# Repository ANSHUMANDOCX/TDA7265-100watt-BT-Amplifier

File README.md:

# TDA7265 100 watt DUAL IC BT Amplifier 

This is a BT amp which has a max ouput of 100watt (50+50) and BT input for audio

# Parts
- TDA7265 IC x2
- MH-M18
- 12-0-12 Transformer

# Plan
I always wanted to make a powerful enough speakers to use with my Sony speaker. Now i have found a appropriate ic which can be tweaked to to get a max output of 50 watt in each channel hence 100watt total TDP.

I have use a MH-M18 BT module which is both cheap and provides lossless audio

i had made a TDA7269A amp which was a 14+14 watt Amp so this is a massive upgrade to it.

# BOM
| S.No | Description                       | Quantity | Total Price | Supplier |LINK|
|------|-----------------------------------|----------|-------------|----------|-------------------------------|
| 1    | Capacitors |         | $3.64       | LCSC    |https://lcsc.com/product-detail/Aluminum-Electrolytic-Capacitors-Leaded_AISHI-ERR1VM102G20OT_C398835.html  https://lcsc.com/product-detail/image/50YXF1MEFC5X11_C2927584.html  https://lcsc.com/product-detail/Aluminum-Electrolytic-Capacitors-Leaded_Rubycon-50YXF1MEFC5X11_C2927584.html  https://lcsc.com/product-detail/Aluminum-Electrolytic-Capacitors-Leaded_Rubycon-50YXF10MEFC5X11_C88726.htmldc  https://lcsc.com/product-detail/Film-Capacitors_KYET-PE104J2A0501_C390170.html  https://lcsc.com/product-detail/Film-Capacitors_WEIDY-W242A562JD2TAAA4JA_C7502419.html|
| 2    | Resistor  | 5        | $3.03       | LCSC    |https://lcsc.com/product-detail/Through-Hole-Resistors_VO-MF1-4W-36K-1-ST52_C2848587.html  https://lcsc.com/product-detail/Through-Hole-Resistors_YAGEO-MFR-25FBF52-560R_C1369978.html  https://lcsc.com/product-detail/Through-Hole-Resistors_CCO-Chian-Chia-Elec-CF1-4W-4-7-5-T_C119999.html  https://lcsc.com/product-detail/Through-Hole-Resistors_Huaxing-Mechanical-Elec-MF1-4W-1K-1-T52_C713997.html  https://lcsc.com/product-detail/Through-Hole-Resistors_VO-MF1-4W-10K-1-ST52_C2903232.html|
| 3    | Diode   | 5        | $0.81      | LCSC    |https://lcsc.com/product-detail/Diodes-General-Purpose_LGE-6A4_C5369359.html|
| 4    | Regulator ICs | 5        | $2.77       | LCSC    |https://lcsc.com/product-detail/Voltage-Regulators-Linear-Low-Drop-Out-LDO-Regulators_ST-L7912CV-DG_C3797.html  https://lcsc.com/product-detail/Voltage-Regulators-Linear-Low-Drop-Out-LDO-Regulators_ST-L7812CV-DG_C2914.html  https://lcsc.com/product-detail/Voltage-Regulators-Linear-Low-Drop-Out-LDO-Regulators_ST-L7805CV-DG_C3795.html|
| 5    |TDA7265 | 2        | $3       | LCSC              |https://lcsc.com/product-detail/E-ink-Display_SEEKINK-E037A49_C41416467.html?s_z=n_C41416467|
| 6    |Terminal Blocks | —        | $2.32       | LCSC    |https://lcsc.com/product-detail/Screw-Terminal-Blocks_JILN-JL500-50802G01_C709041.html  https://lcsc.com/product-detail/Screw-Terminal-Blocks_Ningbo-Kangnex-Elec-WJ500V-5-08-3P_C72334.html|
||TRANSFORMER+BT MODLUE+WIRE||$18 |Maker Bazaar|https://makerbazar.in/products/multi-coloured-ribbon-cable-wire?variant=40914910281879  https://makerbazar.in/products/wireless-bluetooth-audio-receiver-module?variant=46233436946672  https://makerbazar.in/products/24volt-dc-switch-mode-power-supply-smps-rectangular-metal-casing?variant=47589077188848 |
|||SHIPPING LCSC|3.75|LCSC||
|||PCB+ Shipping|12|JLCPCB||
|||**TOTAL**|48.42||

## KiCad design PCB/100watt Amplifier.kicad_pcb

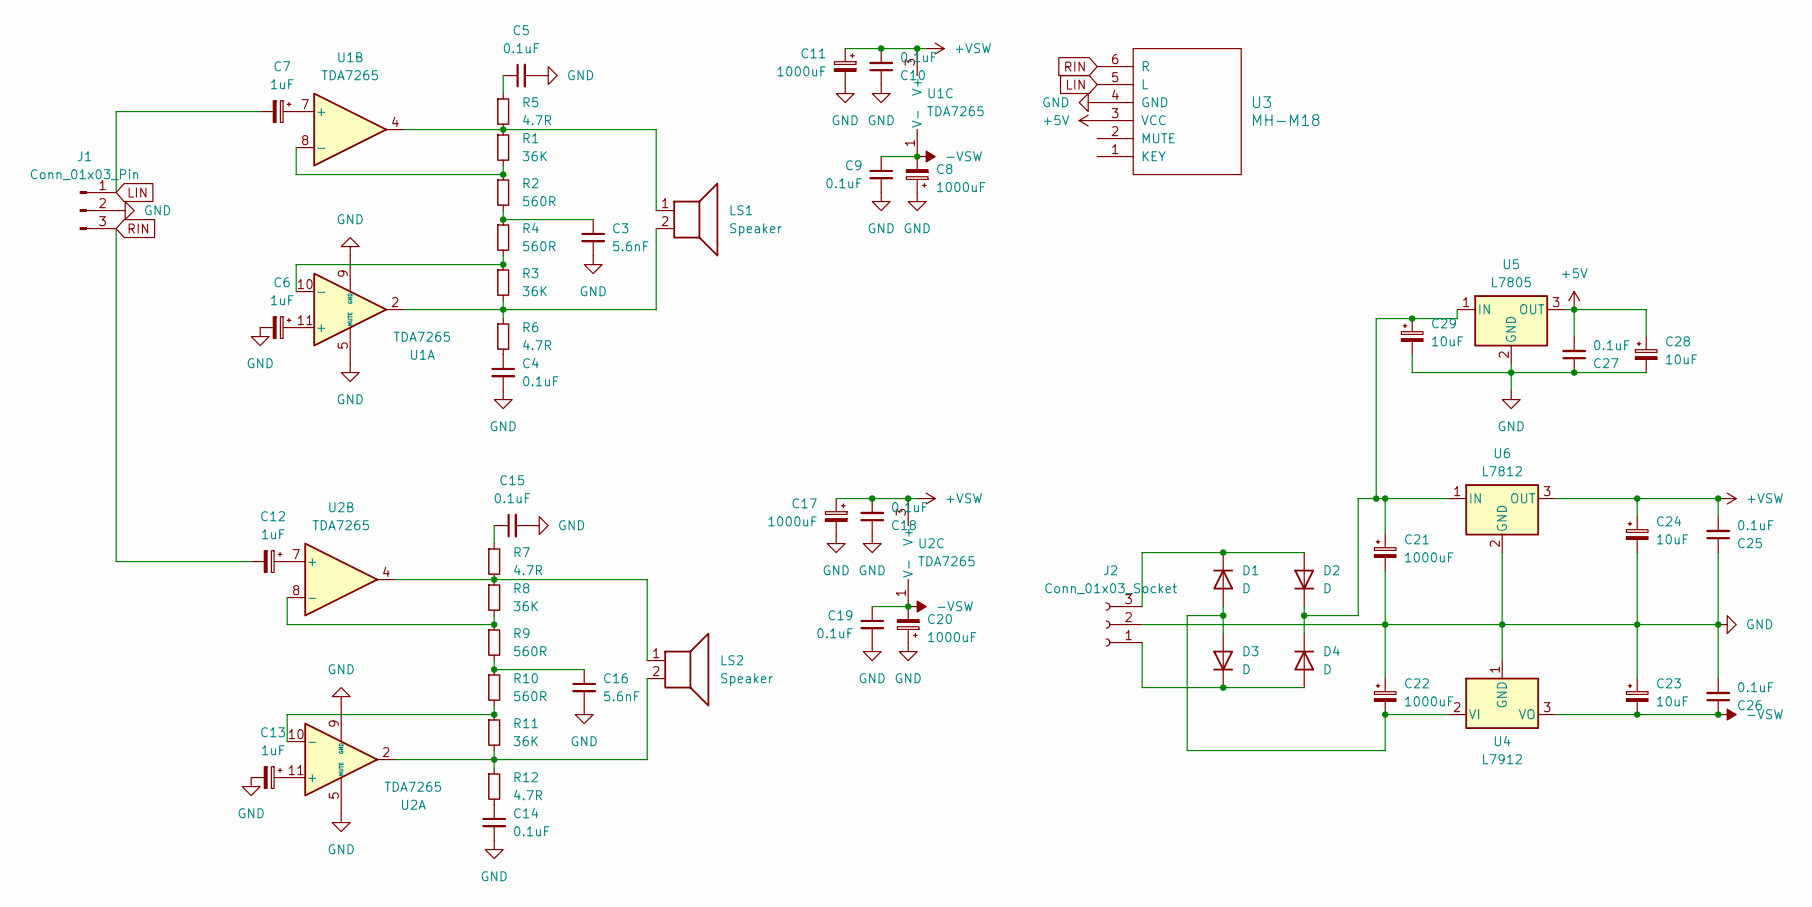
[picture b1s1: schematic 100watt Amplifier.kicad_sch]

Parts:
C3, C16: 5.6nF; C_Rect_L7.2mm_W2.5mm_P5.00mm_FKS2_FKP2_MKS2_MKP2
C4, C5, C9, C10, C14, C15, C18, C19, C25, C26, C27: 0.1uF; C_Rect_L7.2mm_W2.5mm_P5.00mm_FKS2_FKP2_MKS2_MKP2
C6, C7, C12, C13: 1uF; CP_Radial_D5.0mm_P2.00mm
C8, C11, C17, C20, C21, C22: 1000uF; CP_Radial_D10.0mm_P5.00mm
C23, C24, C28, C29: 10uF; CP_Radial_D5.0mm_P2.00mm
D1, D2, D3, D4: D; D_P600_R-6_P20.00mm_Horizontal
J1: Conn_01x03_Pin; PJ-3200
J2: Conn_01x03_Socket; TerminalBlock_bornier-3_P5.08mm
LS1, LS2: Speaker; TerminalBlock_bornier-2_P5.08mm
R1, R3, R8, R11: 36K; R_Axial_DIN0207_L6.3mm_D2.5mm_P10.16mm_Horizontal
R2, R4, R9, R10: 560R; R_Axial_DIN0207_L6.3mm_D2.5mm_P10.16mm_Horizontal
R5, R6, R7, R12: 4.7R; R_Axial_DIN0207_L6.3mm_D2.5mm_P10.16mm_Horizontal
U1, U2: TDA7265; TO-220-11_P3.4x5.08mm_StaggerOdd_Lead4.85mm_Vertical
U3: MH-M18
U4: L7912; TO-220-3_Vertical
U5: L7805; TO-220-3_Vertical
U6: L7812; TO-220-3_Vertical

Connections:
+5V: C27.2, C28.1, U3.3 (VCC), U5.3 (OUT)
+VSW: C10.2, C11.1, C17.1, C18.2, C24.1, C25.2, U1.3 (V+), U2.3 (V+), U6.3 (OUT)
-VSW: C8.2, C9.1, C19.1, C20.2, C23.2, C26.1, U1.1 (V-), U1.6 (V-), U2.1 (V-), U2.6 (V-), U4.3 (VO)
GND: C3.2, C4.2, C5.2, C6.2, C8.1, C9.2, C10.1, C11.2, C13.2, C14.2, C15.2, C16.2, C17.2, C18.1, C19.2, C20.1, C21.2, C22.1, C23.1, C24.2, C25.1, C26.2, C27.1, C28.2, C29.2, J1.2, J2.2, U1.5 (MUTE), U1.9 (GND), U2.5 (MUTE), U2.9 (GND), U3.4 (GND), U4.1 (GND), U5.2 (GND), U6.2 (GND)
LIN: C7.2, J1.1, U3.5 (L)
unnamed: C3.1, R2.2, R4.1
unnamed: C4.1, R6.2
unnamed: C5.1, R5.1
unnamed: C14.1, R12.2
unnamed: C15.1, R7.1
unnamed: C16.1, R9.2, R10.1
unnamed: C22.2, D1.2 (A), D3.2 (A), U4.2 (VI)
unnamed: D1.1 (K), D2.2 (A), J2.3
unnamed: C21.1, C29.1, D2.1 (K), D4.1 (K), U5.1 (IN), U6.1 (IN)
unnamed: D3.1 (K), D4.2 (A), J2.1
unnamed: LS1.1, R1.1, R5.2, U1.4
unnamed: LS1.2, R3.2, R6.1, U1.2
unnamed: LS2.1, R7.2, R8.1, U2.4
unnamed: LS2.2, R11.2, R12.1, U2.2
unnamed: C6.1, U1.11 (+)
unnamed: R3.1, R4.2, U1.10 (-)
unnamed: C7.1, U1.7 (+)
unnamed: R1.2, R2.1, U1.8 (-)
unnamed: C13.1, U2.11 (+)
unnamed: R10.2, R11.1, U2.10 (-)
unnamed: C12.1, U2.7 (+)
unnamed: R8.2, R9.1, U2.8 (-)
RIN: C12.2, J1.3, U3.6 (R)

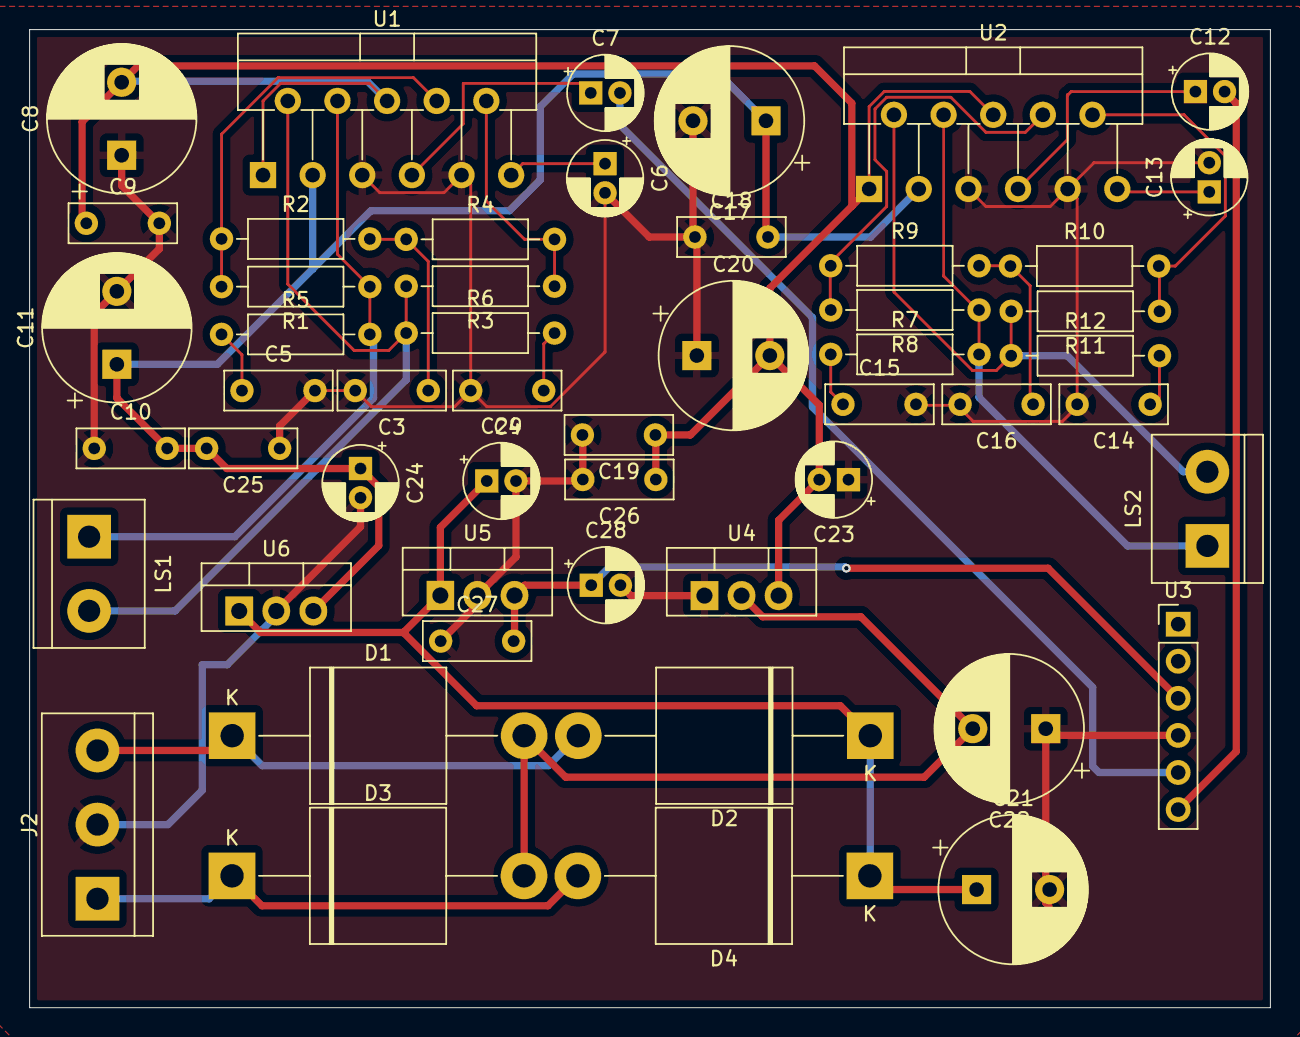
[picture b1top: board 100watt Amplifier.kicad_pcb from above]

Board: 2 copper layers, 85.0 x 67.0 mm, 52 parts (0 on the bottom side), 28 nets.
